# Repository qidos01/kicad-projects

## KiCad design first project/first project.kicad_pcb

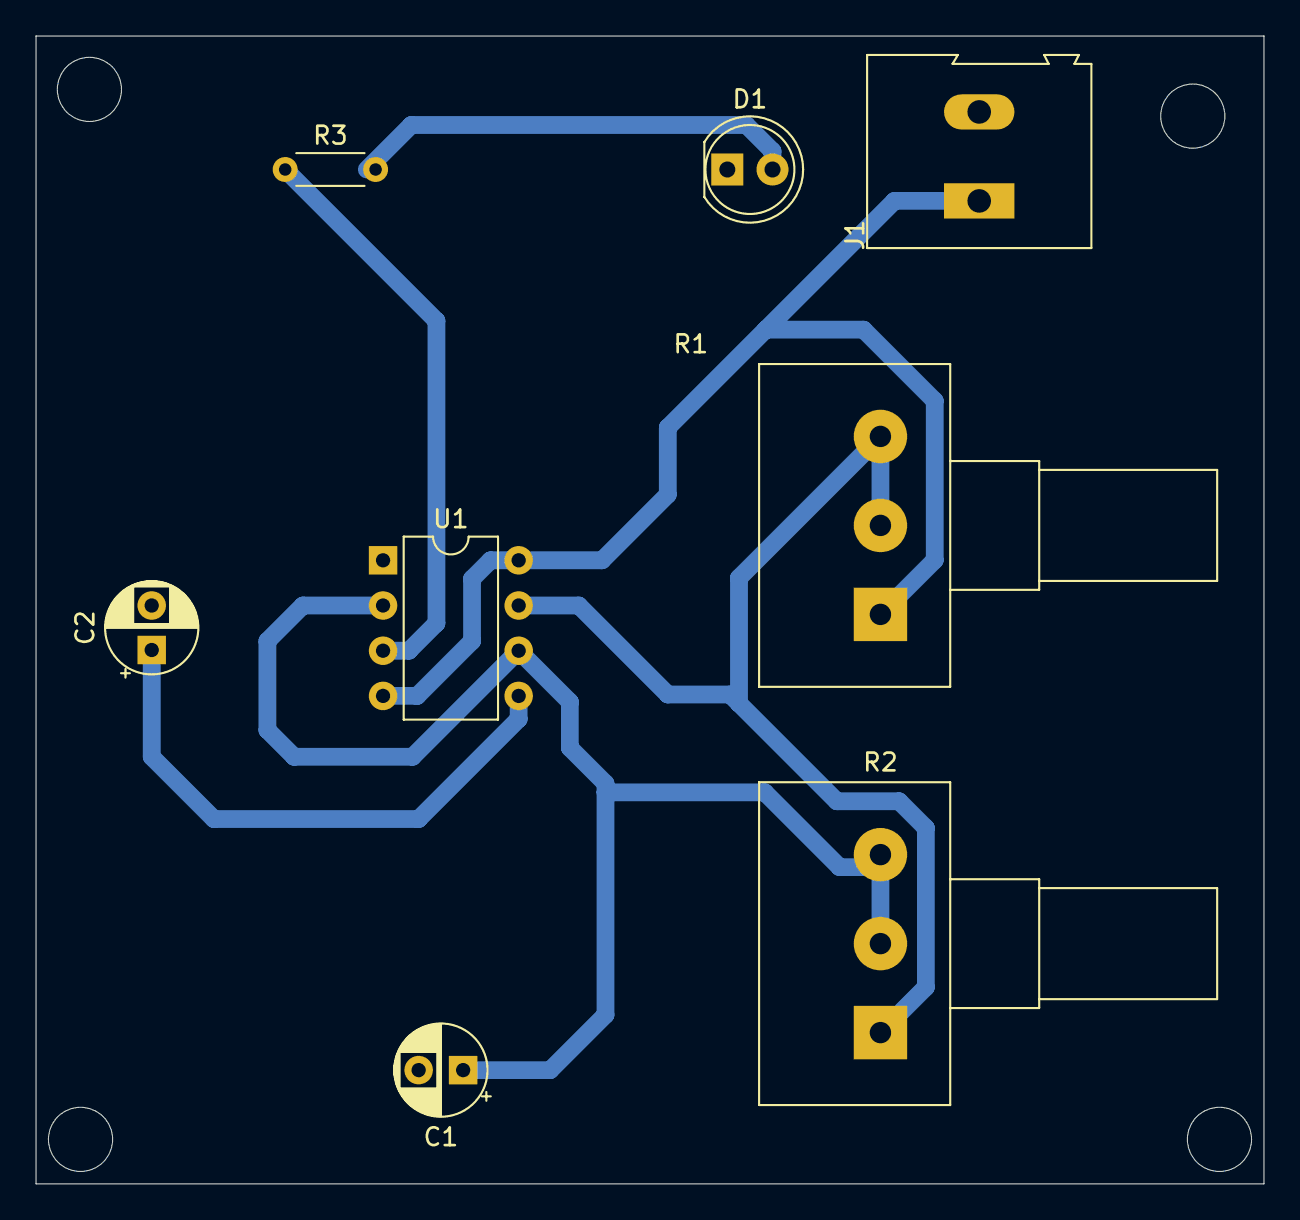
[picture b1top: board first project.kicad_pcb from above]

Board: 2 copper layers, 69.0 x 64.5 mm, 8 parts (0 on the bottom side), 7 nets.

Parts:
C1: 0.1u; CP_Radial_D5.0mm_P2.50mm
C2: C; CP_Radial_D5.0mm_P2.50mm
D1: LED; LED_D5.0mm
J1: OSTTC020162; TerminalBlock_Altech_AK300-2_P5.00mm
R1, R2: R_US; Potentiometer_Alps_RK163_Single_Horizontal
R3: R_US; R_Axial_DIN0204_L3.6mm_D1.6mm_P5.08mm_Horizontal
U1: NE555P; DIP-8_W7.62mm

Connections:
+5V: J1.1, R1.1, U1.4 (R), U1.8 (VCC)
Earth: C1.2, C2.2, D1.1 (K), J1.2, U1.1 (GND)
unnamed: D1.2 (A), R3.2
unnamed: C2.1, U1.5 (CV)
unnamed: R1.2, R1.3, R2.1, U1.7 (DIS)
unnamed: R3.1, U1.3 (Q)
unnamed: C1.1, R2.2, R2.3, U1.2 (TR), U1.6 (THR)
